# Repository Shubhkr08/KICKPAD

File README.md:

# KICKPAD

This is a Xiao Rp2040  Based MicroPad , It has 9 Switches , a roter encode and a oled screen . We used matrix for switches so it uses less gpio pins and it has 4 layers the rotor key is used to change the layers which is displaced on the screen so in total we have  keys output 9x4=36 + 4 outputs from rotor = 40 Outputs.
## Features

- Based on Xiao Rp2040
- Has total 40 Outputs
## Firmware
- Firmware is based on QMK.

- ### Schematic<br><br>

###  PCB Design<br><br>

### 3D Design <br><br>

# Bill of Materials (BOM)

## Components

| Qty | Part Description | Link | Cost (USD) |
|-----|------------------|------|-------------|
| 1 | Xiao RP2040 + Rotary Encoder | — | Already have |
| 10 | Diodes | — | Already have |
| 10 | Kailh Hot-Swap Switch Sockets + shipping | https://meckeys.com/shop/accessories/keyboard-accessories/key-switches/kailh-hot-swap-socket/ | 1.95 |
| 1 | Keycaps and Switches | — | Already have |

---

## Manufacturing & Shipping

| Item | Link | Cost (USD) |
|------|------|-------------|
| PCB Fabrication + 3D Print + Shipping | https://jlcpcb.com | 20.27 |

---

# Total Project Cost

| Category | Cost (USD) |
|----------|-------------|
| Components Purchased | 1.95 |
| PCB + 3D Print + Shipping | 20.27 |
| **Grand Total** | **22.22 USD** |

---

## Final Total: **$22.22 USD**

> *Parts marked as “Already have” were not included in the total project cost.*

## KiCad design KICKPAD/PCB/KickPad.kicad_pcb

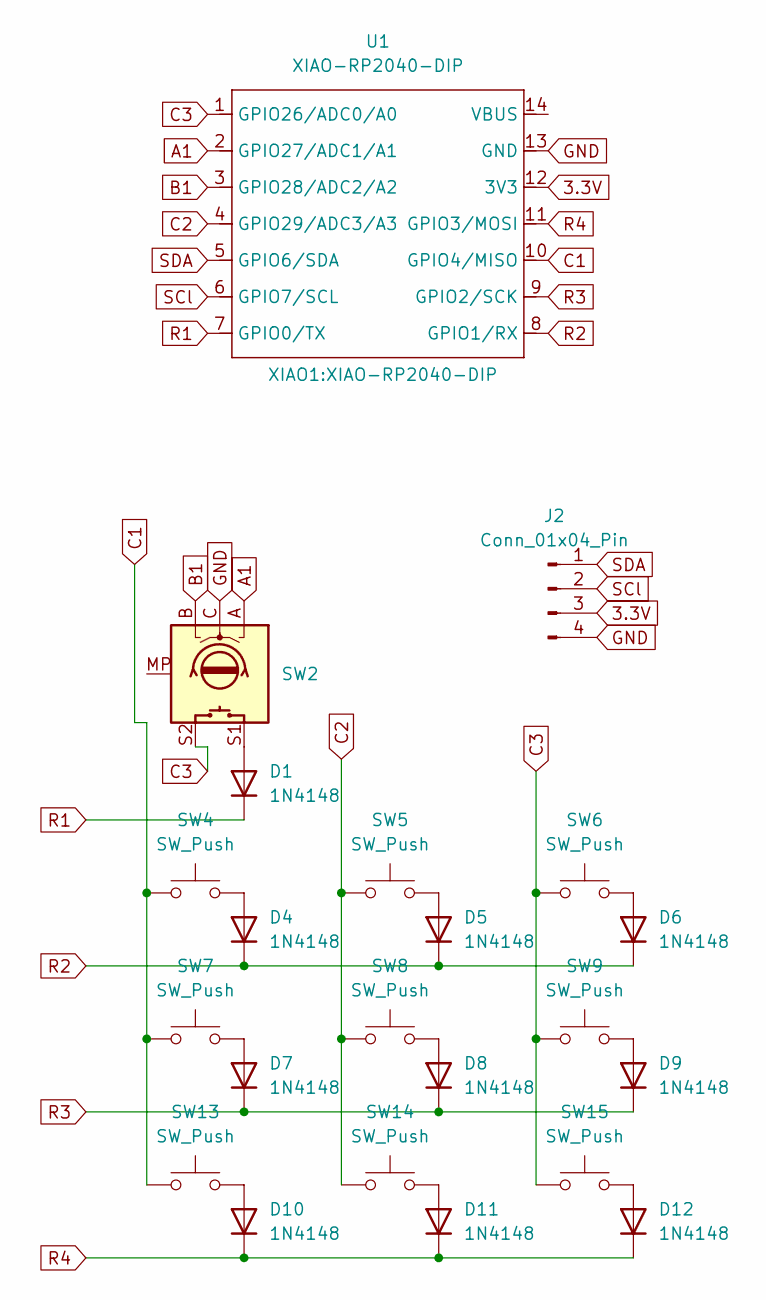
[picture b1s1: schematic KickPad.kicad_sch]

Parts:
D1, D4, D5, D6, D7, D8, D9, D10, D11, D12: 1N4148; D_DO-35_SOD27_P7.62mm_Horizontal
J2: Conn_01x04_Pin; OLED_128x32
SW2: RotaryEncoder_Switch_MP; RotaryEncoder_Alps_EC11E-Switch_Vertical_H20mm
SW4, SW5, SW6, SW7, SW8, SW9, SW13, SW14, SW15: SW_Push; MX100H
U1: XIAO-RP2040-DIP

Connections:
3.3V: J2.3, U1.12 (3V3)
A1: SW2.A, U1.2 (GPIO27/ADC1/A1)
B1: SW2.B, U1.3 (GPIO28/ADC2/A2)
C1: SW4.1, SW7.1, SW13.1, U1.10 (GPIO4/MISO)
C2: SW5.1, SW8.1, SW14.1, U1.4 (GPIO29/ADC3/A3)
C3: SW2.S2, SW6.1, SW9.1, SW15.1, U1.1 (GPIO26/ADC0/A0)
GND: J2.4, SW2.C, U1.13 (GND)
unnamed: D1.2 (A), SW2.S1
unnamed: D4.2 (A), SW4.2
unnamed: D5.2 (A), SW5.2
unnamed: D6.2 (A), SW6.2
unnamed: D7.2 (A), SW7.2
unnamed: D8.2 (A), SW8.2
unnamed: D9.2 (A), SW9.2
unnamed: D10.2 (A), SW13.2
unnamed: D11.2 (A), SW14.2
unnamed: D12.2 (A), SW15.2
R1: D1.1 (K), U1.7 (GPIO0/TX)
R2: D4.1 (K), D5.1 (K), D6.1 (K), U1.8 (GPIO1/RX)
R3: D7.1 (K), D8.1 (K), D9.1 (K), U1.9 (GPIO2/SCK)
R4: D10.1 (K), D11.1 (K), D12.1 (K), U1.11 (GPIO3/MOSI)
SCl: J2.2, U1.6 (GPIO7/SCL)
SDA: J2.1, U1.5 (GPIO6/SDA)

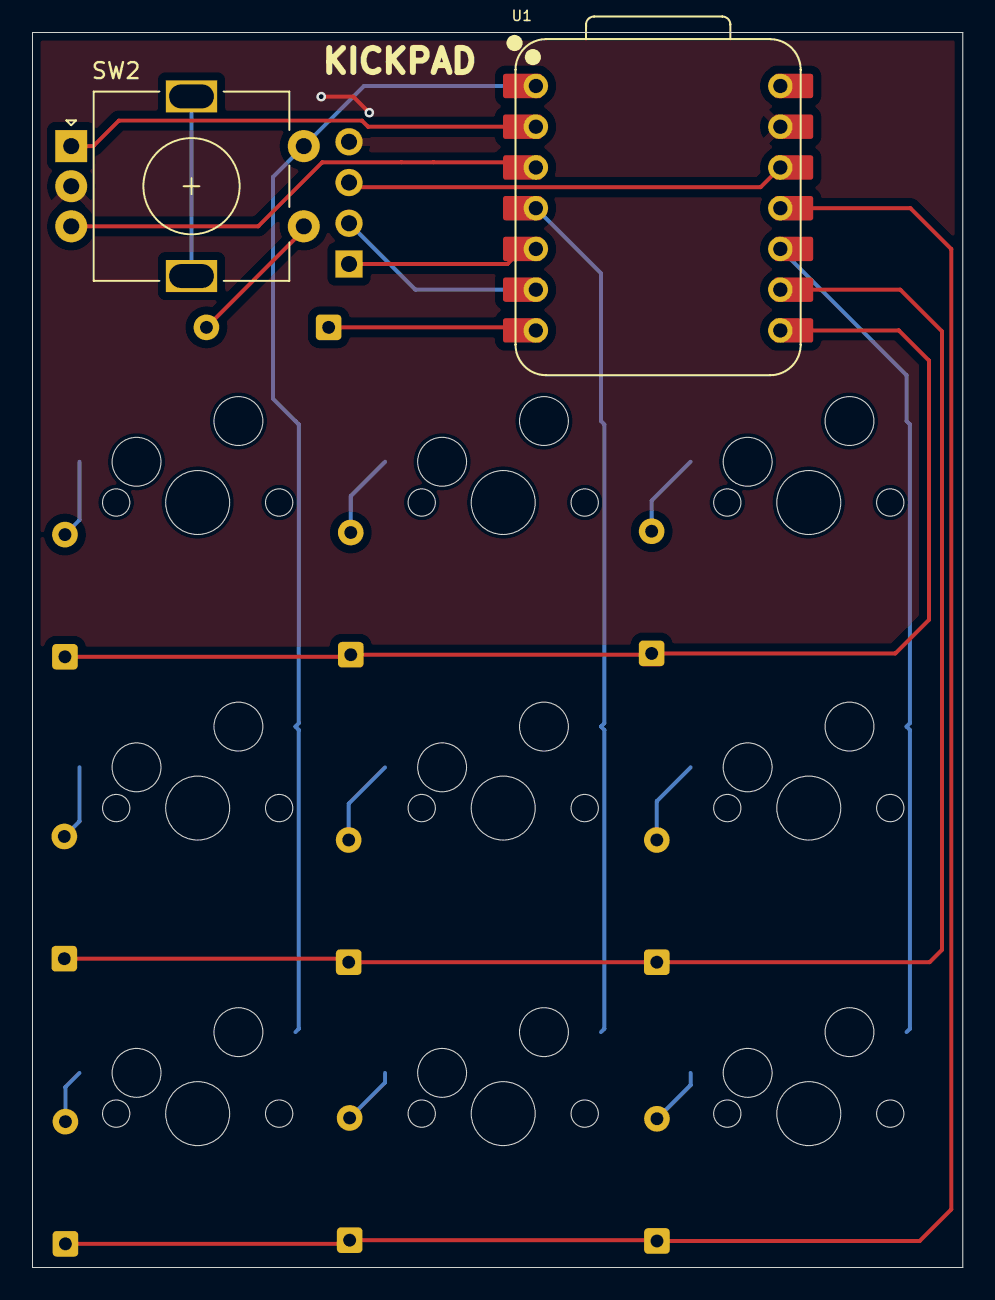
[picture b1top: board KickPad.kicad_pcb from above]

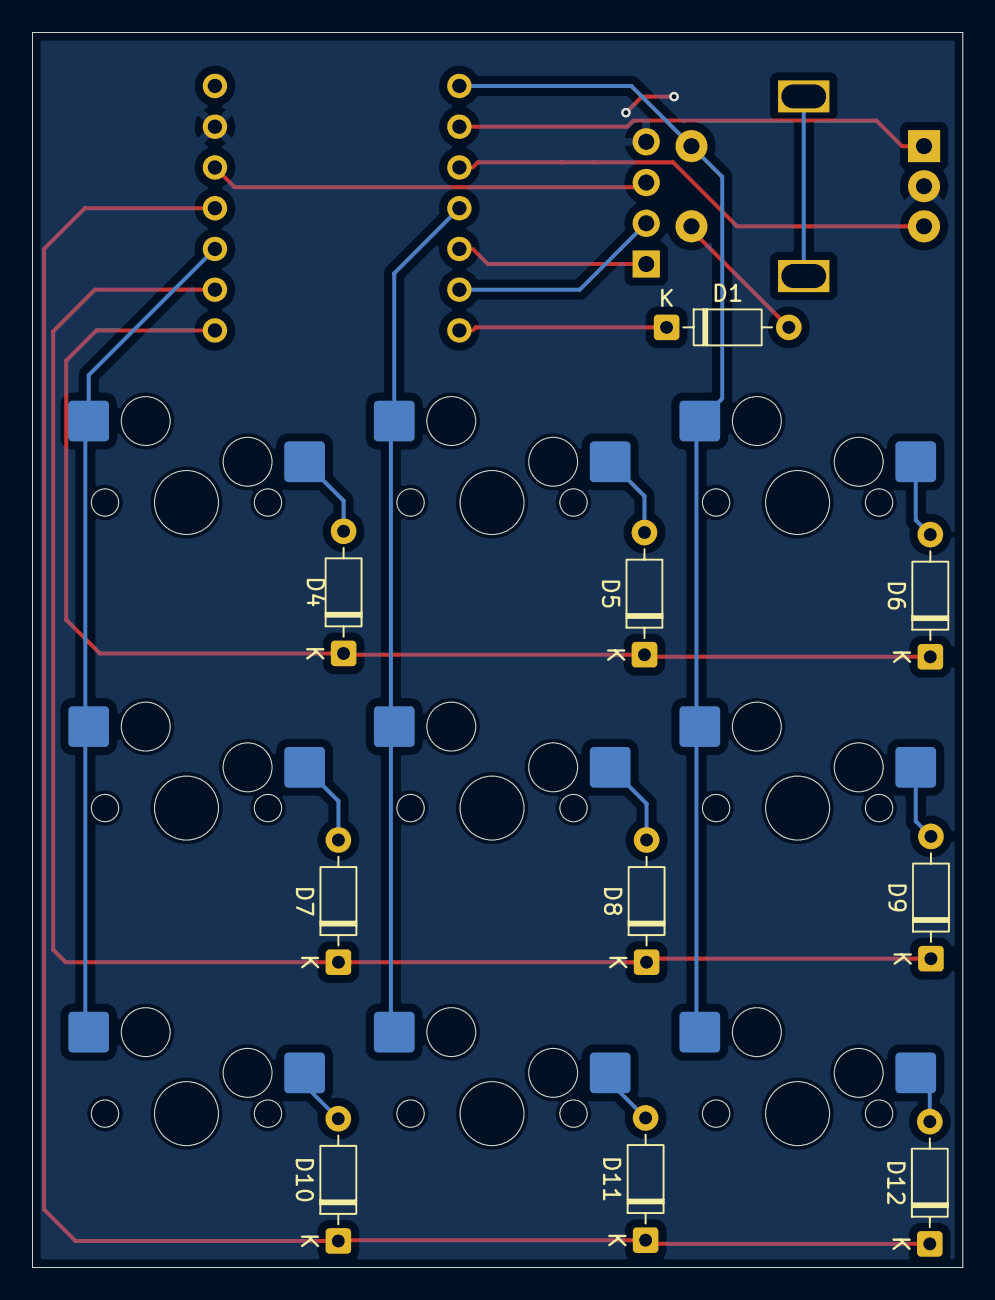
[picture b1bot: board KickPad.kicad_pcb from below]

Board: 2 copper layers, 58.0 x 77.0 mm, 22 parts (19 on the bottom side), 23 nets.

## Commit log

2026-05-08 Create BOM.
2026-05-08 Update BOM.
